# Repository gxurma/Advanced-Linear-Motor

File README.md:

# Advanced-Linear-Motor

An advanced design for linear motors. Uses also some advanced algorithms and Python scripts to optimize the copper usage, resistance, and heat dissipation.

# Design goals

- 6 layer PCBs
- 70µm or 105µm thick copper
- Maximized copper packing for efficiency
- 3 phases
- 1 phase spans 2 layers
- Minimize the number of via

# Adjustable Parameters
The following parameters can be adjusted to customize the design:

- **number_of_tracks_per_pole**: Defines the number of tracks within a single pole.
- **clearance**: Minimum spacing between tracks, in millimeters.

These parameters can be found and adjusted in the `CONFIG` section of the code.

# PCB Parameters

- **pcb_length_mm**: Length of the PCB area dedicated to the tracks (in mm).
- **pcb_height_mm**: Height of the PCB area dedicated to the tracks (in mm).
- **no_of_poles**: Total number of poles in the design.
- **no_of_periods**: Number of repeating periods for the track layout.
- **no_of_phases**: Number of electrical phases (e.g., 3-phase motor).

# Installation

1. Clone the repository:
   ```bash
   git clone <repository-url>
   ```
2. Place the plugin in KiCad's scripting plugins directory:
   - Windows: `%APPDATA%/kicad/scripting/plugins/`
   - Linux: `~/.local/share/kicad/scripting/plugins/`
   - macOS: `~/Library/Application Support/kicad/scripting/plugins/`
3. Restart KiCad to load the plugin.

# Usage

1. Open your PCB project in KiCad.
2. Launch the plugin from **Tools > External Plugins**.
3. Adjust the design parameters as needed:
   - Track width, clearance, via dimensions
   - Number of poles and phases
4. Click **Run Plugin** to generate the layout.

# Examples with Different Parameters

## Example 1: Lower Number of Tracks
This example uses a lower value for `number_of_tracks_per_pole`. The clearance is kept at 0.25 mm.

## Example 2: Higher Number of Tracks
This example increases the `number_of_tracks_per_pole` and the clearance is kept at 0.25 mm.

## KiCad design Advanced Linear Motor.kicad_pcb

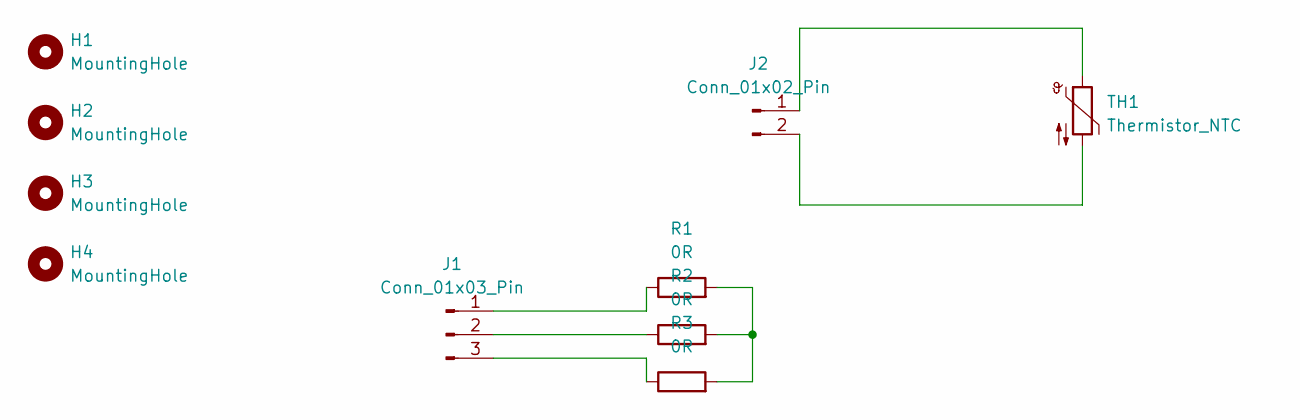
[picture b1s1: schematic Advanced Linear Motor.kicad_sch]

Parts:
H1, H2, H3, H4: MountingHole; MountingHole_3.2mm_M3_DIN965
J1: Conn_01x03_Pin; JST_XH_B3B-XH-A_1x03_P2.50mm_Vertical
J2: Conn_01x02_Pin; JST_XH_B2B-XH-A_1x02_P2.50mm_Vertical
R1, R2, R3: 0R; R_0805_2012Metric_Pad1.20x1.40mm_HandSolder
TH1: Thermistor_NTC; R_0805_2012Metric_Pad1.20x1.40mm_HandSolder

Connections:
unnamed: J1.1, R1.1
unnamed: J1.2, R2.1
unnamed: J1.3, R3.1
unnamed: J2.1, TH1.1
unnamed: J2.2, TH1.2
unnamed: R1.2, R2.2, R3.2

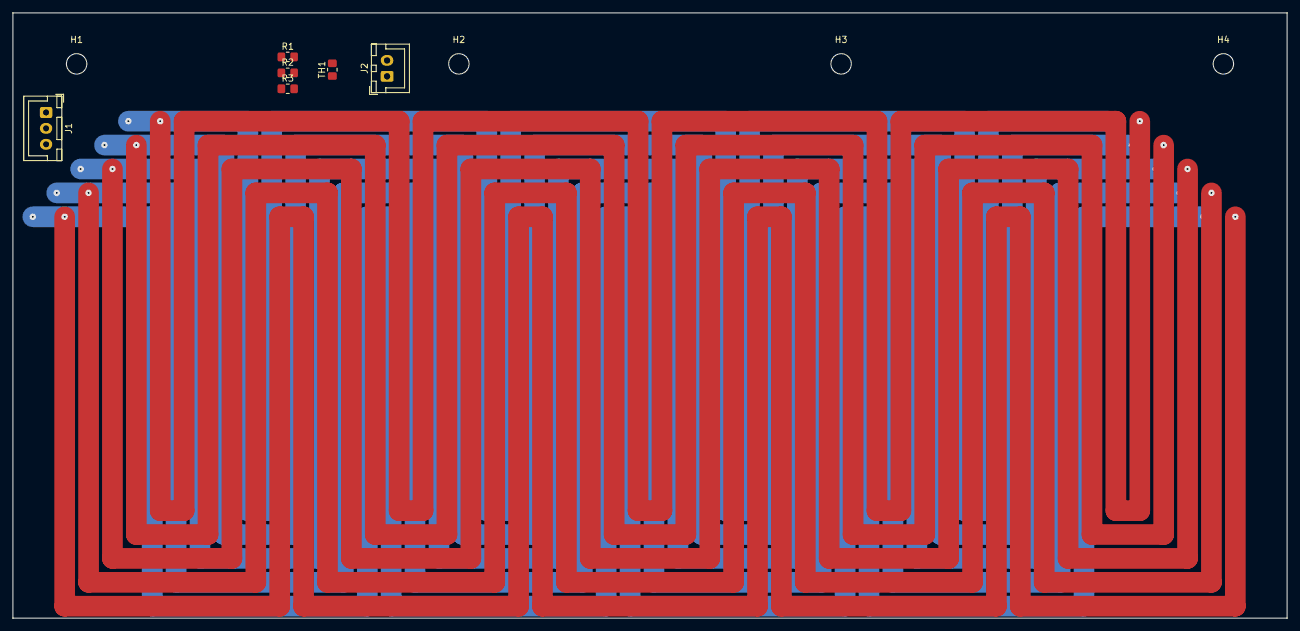
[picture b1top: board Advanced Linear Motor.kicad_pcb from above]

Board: 6 copper layers, 200.0 x 95.0 mm, 10 parts (0 on the bottom side), 6 nets.

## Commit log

2024-07-27 first commit: So oder ähnlich solls mal aussehen
2024-08-22 add skeleton
2024-08-22 test some code
2024-08-23 add basic geometrical data to constructor
2024-11-29 u shapes
2024-12-01 incomplete u shapes for on half phase
2024-12-01 forward and backward phase tracks with vias
2024-12-02 3 phase
2024-12-03 logic is working - quality verbesserung
2024-12-03 update reamde
2024-12-04 v1_ready
2024-12-04 readme fix
2024-12-04 readme update
